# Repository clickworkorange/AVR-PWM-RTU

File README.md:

- <a href="#description">Description</a>
- <a href="#register-map">Register map</a>
- <a href="#avr-pin-map">AVR pin map</a>
- <a href="#defaults">Defaults</a>
- <a href="#crystal-selection">Crystal selection</a>
- <a href="#schematic">Schematic</a>
- <a href="#pcb-layout">PCB layout</a>
- <a href="#the-remote-panels">The remote panels</a>
- <a href="#future">Future</a>
- <a href="#wetware-at-work">Wetware at work</a>

### Description
A Modbus and push-button controlled 4-channel PWM generator based on the Atmel ATMega328. Each channel can be set to one of four pre-defined duty cycles (0-255). In addition to being controllable by Modbus commands, the channel levels (0-3) can also be selected by means of individual push-buttons, wich increment a channel's level, wrapping at 3. The active level for each channel is output as a 2-bit value which is used to drive a set of four LEDs by means of a 74HC238 decoder. The idea is to allow for remote control of the individual channels over a three-wire interface (plus GND and VCC). The Modbus communication layer is provided by the <a href="https://github.com/mbs38/yaMBSiavr">yaMBSiavr</a> library. The code compiles to 9.3kB. 

*N.b. this is still work in progress and some features are yet to be implemented - see <a href="#future">future</a>.*

### Register map
Modbus register values are limited to a maximum value for each register; attempting to write a higher value than what is permitted for a given register will return a 03 ILLEGAL DATA VALUE response from the RTU. The same will happen if you try to write to a read only register. Writing a 1 to the last register (currently 50) will trigger a save to EEPROM of all register values - the RTU will revert to these stored values on reboot. 

#|Function|Value| |#|Function|Value
--|-------------|-----|-|--|-------------|-----
0|Ch0 Level|0-3| |26|Device ID 4-5|2 bytes
1|Ch1 Level|0-3| |27|Device ID 6-7|2 bytes
2|Ch2 Level|0-3| |28|Ch0 ID 0-1|2 bytes
3|Ch3 Level|0-3| |29|Ch0 ID 2-3|2 bytes
4|Ch0 Duty 0|0-255| |30|Ch0 ID 4-5|2 bytes
5|Ch0 Duty 1|0-255| |31|Ch0 ID 6-7|2 bytes
6|Ch0 Duty 2|0-255| |32|Ch1 ID 0-1|2 bytes
7|Ch0 Duty 3|0-255| |33|Ch1 ID 2-3|2 bytes
8|Ch1 Duty 0|0-255| |34|Ch1 ID 4-5|2 bytes
9|Ch1 Duty 1|0-255| |35|Ch1 ID 6-7|2 bytes
10|Ch1 Duty 2|0-255| |36|Ch2 ID 0-1|2 bytes
11|Ch1 Duty 3|0-255| |37|Ch2 ID 2-3|2 bytes
12|Ch2 Duty 0|0-255| |38|Ch2 ID 4-5|2 bytes
13|Ch2 Duty 1|0-255| |39|Ch2 ID 6-7|2 bytes
14|Ch2 Duty 2|0-255| |40|Ch3 ID 0-1|2 bytes
15|Ch2 Duty 3|0-255| |41|Ch3 ID 2-3|2 bytes
16|Ch3 Duty 0|0-255| |42|Ch3 ID 4-5|2 bytes
17|Ch3 Duty 1|0-255| |43|Ch3 ID 6-7|2 bytes
18|Ch3 Duty 2|0-255| |44|Slave Address|0-255
19|Ch3 Duty 3|0-255| |45|Baud Rate|0-7
20|Ch0-1 Invert|0-1| |46|Parity|0-2
21|Ch0-1 Scaler|0-7*| |47|Stop Bits|0-1
22|Ch2-3 Invert|0-1| |48|Firmware Revision|-
23|Ch2-3 Scaler|0-7*| |49|*Reserved*|
24|Device ID 0-1|2 bytes| |50|Save Settings|1/0
25|Device ID 2-3|2 bytes| | | |

\*) See the below table for the meaning of the scaler values:

**Value**|0|1|2|3|4|5|6|7
-----|----|----|----|----|----|----|----|----
**Scaler**|0|1|8|32|64|128|256|1024

Setting either of the scaler registers to zero disables those two channels. See <a href="#crystal-selection">Crystal selection</a> for the PWM frequencies resulting from the different prescalers. Note that at present changes to scalers, inversion and communication parameters requires rebooting the RTU for the changes to take effect. 

### AVR pin map

Pin|Port|Function| |Pin|Port|Function
---|----|-------------|-|---|----|-------------
1|PC6|Reset| |15|PB1|Ch0 PWM
2|PD0|RxD| |16|PB2|Ch1 PWM
3|PD1|TxD| |17|PB3|Ch2 PWM
4|PD2|Data Dir| |18|PB4|Ch3 Lvl LSB
5|PD3|Ch3 PWM| |19|PB5|Ch3 Lvl MSB
6|PD4|Load Defaults| |20|AVCC|+5V
7|Vcc|+5V| |21|AREF|n/c
8|GND|GND| |22|GND|GND
9|PB6|Xtal| |23|PC0|Ch0 Lvl LSB
10|PB7|Xtal| |24|PC1|Ch0 Lvl MSB
11|PD5|Ch2 Btn| |25|PC2|Ch0 Btn
12|PD6|Ch2 Lvl LSB| |26|PC3|Ch1 Lvl LSB
13|PD7|Ch2 Lvl MSB| |27|PC4|Ch1 Lvl MSB
14|PB0|Ch3 Btn| |28|PC5|Ch1 Btn

### Defaults
The default configuration values are: 

- Channel levels all set to 0
- Duty values for levels (all channels)
	- 0: 255
	- 1: 127
	- 2: 63
	- 3: 0
- Both scaler registers set to 4 (490 Hz @ 8 MHz)
- Communication parameters
	- Slave ID: 1
	- Baud: 9600
	- Parity: None
	- Stop bits: 1
 - Identification strings
 	- Device ID: "PWM-1"
  	- Channel IDs: "Ch0", "Ch1", "Ch2", "Ch3"

The RTU can be reset to these values at any time by holding PD4 low on power on / reset. 

### Crystal selection
It's important to pick a system clock frequency that results in the desired PWM frequency for your particular application. If you are controlling fans or other motor driven devices you'll probably want this to be outside human hearing range, if it's lights you'll want it to be high enough for persistence of vision to hide the flicker. Another consideration is the Baud-rate error that will result from choosing a system clock that is not evenly divisible by the desired communication speed. The table below shows the available PWM frequencies for a given clock and prescaler, with Baud-rate compatible clock speeds highlighted in bold: 

Xtal|1|8|32*|64|128*|256|1024
-----------|--------|--------|--------|--------|--------|--------|--------|
2.0000 MHz|7.8 kHz|980 Hz|245 Hz|123 Hz|61 Hz|31 Hz|8 Hz
**3.6864 MHz**|14.5 kHz|1.8 kHz|452 Hz|226 Hz|113 Hz|56 Hz|14 Hz
4.0000 MHz|15.7 kHz|2.0 kHz|490 Hz|245 Hz|123 Hz|61 Hz|15 Hz
**7.3728 MHz**|28.9 kHz|3.6 kHz|904 Hz|452 Hz|226 Hz|113 Hz|28 Hz
8.0000 MHz|31.4 kHz|3.9 kHz|980 Hz|490 Hz|245 Hz|123 Hz|31 Hz
16.0000 MHz|62.7 kHz|7.8 kHz|2.0 kHz|980 Hz|490 Hz|245 Hz|61 Hz
**18.4320 MHz**|72.3 kHz|9.0 kHz|2.3 kHz|1.1 kHz|565 Hz|282 Hz|71 Hz
20.0000 MHz|78.4 kHz|9.8 kHz|2.5 kHz|1.2 kHz|613 Hz|306 Hz|77 Hz

\*) Prescalers 32 & 128 are not available on Timer1, instead we get these by changing the TOP length to 10-bits / scaler 8 and 9-bits / scaler 64 respectively, and <a href="https://github.com/clickworkorange/AVR-PWM-RTU/blob/cd5e14912393d223fffba5abe3af9f1dc7a8ffb7/AVR/avr_pwm_rtu.c#L113-L127">scaling the 0-255 duty value</a> accordingly. 

### Schematic
The schematic has been updated to revision 0.2 and is now presentable - you can find it in [the /KiCAD folder](https://github.com/clickworkorange/AVR-PWM-RTU/tree/main/KiCAD). There will be more changes, not least on the input side, but this should work: 

See <a href="#the-remote-panels">below</a> for the remote panel schematic & PCB layout. 

### PCB layout
The project includes a PCB layout which is sized to fit in a 3U DIN-rail enclosure: 

I have yet to find a good source for multi-level screw terminals with a 3.5mm pitch, but I know they're out there somewhere! You can find the PCB layout together with the schematic in [the /KiCAD folder](https://github.com/clickworkorange/AVR-PWM-RTU/tree/main/KiCAD). 

### The remote panels
The remote panels consist of push-button and four LEDs indicating the channel's level. The LEDs light up incrementally, with one LED lit for level 0 and all four lit at level 3: 

There is also a tiny PCB for it, just 5x3 cm, which should make it easy to fit wherever you want: 

### Future
#### Must:
* Make comms parameters settable through Modbus registers.
#### Should:
* Make a version for the ATMega328PU.
#### Could:
* Apply PWM frequency scalers without reboot.
* Smooth level transitions. 
* Add additional functions for long-press and double-clicks.
* Use the four additional I/Os on the ATMega328PU for feedback.
* Make an MCU based remote with additional features. 
#### Won't:
* Make PWM frequency continuously variable.
* Replace Modbus with a different protocol. 

### Wetware at work
Resistance may indeed be futile, and I for one welcome our new data-based overlords - who I'm sure are paying close attention. But this software was written by a *human*, and only humans can enjoy writing code. Perhaps that joy by itself will one day be seen as an act of <a href="https://en.wikipedia.org/wiki/Joy_as_an_Act_of_Resistance">resistance</a>?

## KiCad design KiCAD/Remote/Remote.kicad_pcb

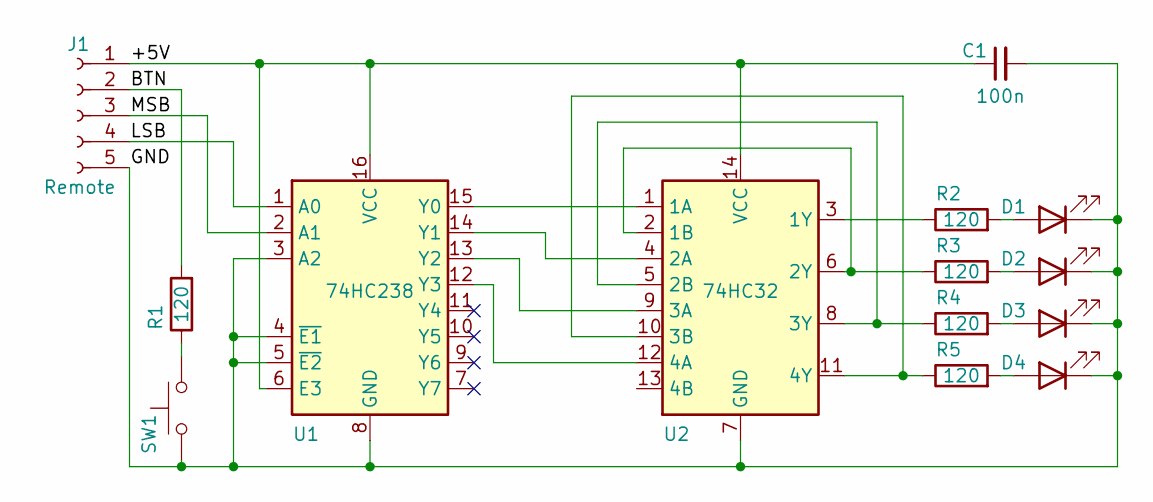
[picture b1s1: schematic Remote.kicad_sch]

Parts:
C1: 100n; C_0805_2012Metric
D1, D2, D3, D4: LED; LED_D3.0mm
J1: Remote; TerminalBlock_Phoenix_PT-1,5-5-3.5-H_1x05_P3.50mm_Horizontal
R1, R2, R3, R4, R5: 120; R_0805_2012Metric
SW1: E-Switch PB300
U1: 74HC238; SOIC-16_3.9x9.9mm_P1.27mm
U2: 74HC32; SOIC-14_3.9x8.7mm_P1.27mm

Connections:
/+5V: C1.1, J1.1, U1.6 (E3), U1.16 (VCC), U2.14 (VCC)
/BTN: J1.2, R1.2
/GND: C1.2, D1.1 (K), D2.1 (K), D3.1 (K), D4.1 (K), J1.5, SW1.1, U1.3 (A2), U1.4 (~E1), U1.5 (~E2), U1.8 (GND), U2.7 (GND)
/LSB: J1.4, U1.1 (A0)
/MSB: J1.3, U1.2 (A1)
unnamed: D1.2 (A), R2.2
unnamed: D2.2 (A), R3.2
unnamed: D3.2 (A), R4.2
unnamed: D4.2 (A), R5.2
unnamed: R1.1, SW1.2
unnamed: R2.1, U2.3 (1Y)
unnamed: R3.1, U2.2 (1B), U2.6 (2Y)
unnamed: R4.1, U2.5 (2B), U2.8 (3Y)
unnamed: U1.12 (Y3), U2.12 (4A)
unnamed: U1.13 (Y2), U2.9 (3A)
unnamed: U1.14 (Y1), U2.4 (2A)
unnamed: U1.15 (Y0), U2.1 (1A)
unnamed: R5.1, U2.10 (3B), U2.11 (4Y)

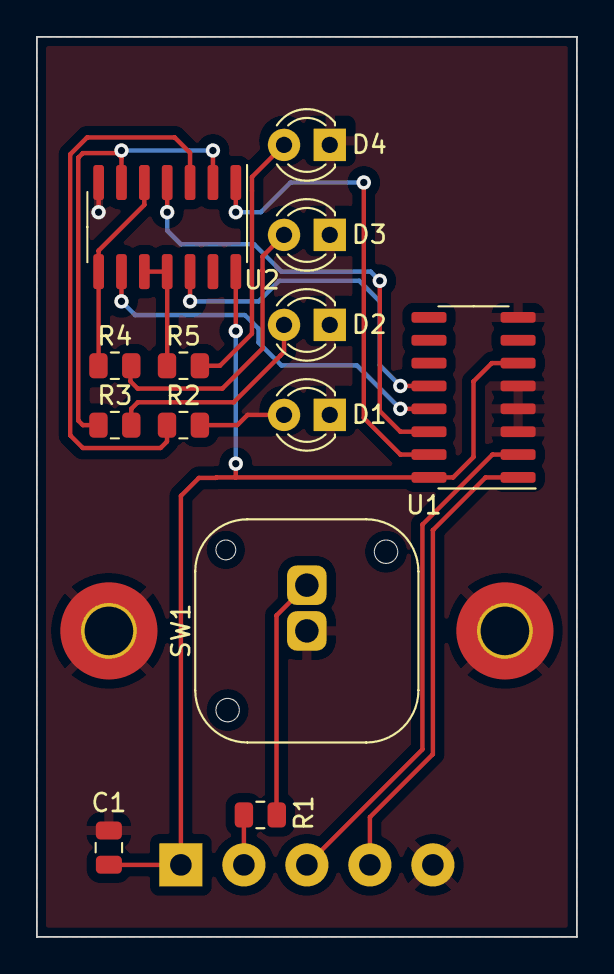
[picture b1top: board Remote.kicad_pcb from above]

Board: 2 copper layers, 30.0 x 50.0 mm, 14 parts (1 on the bottom side), 18 nets.

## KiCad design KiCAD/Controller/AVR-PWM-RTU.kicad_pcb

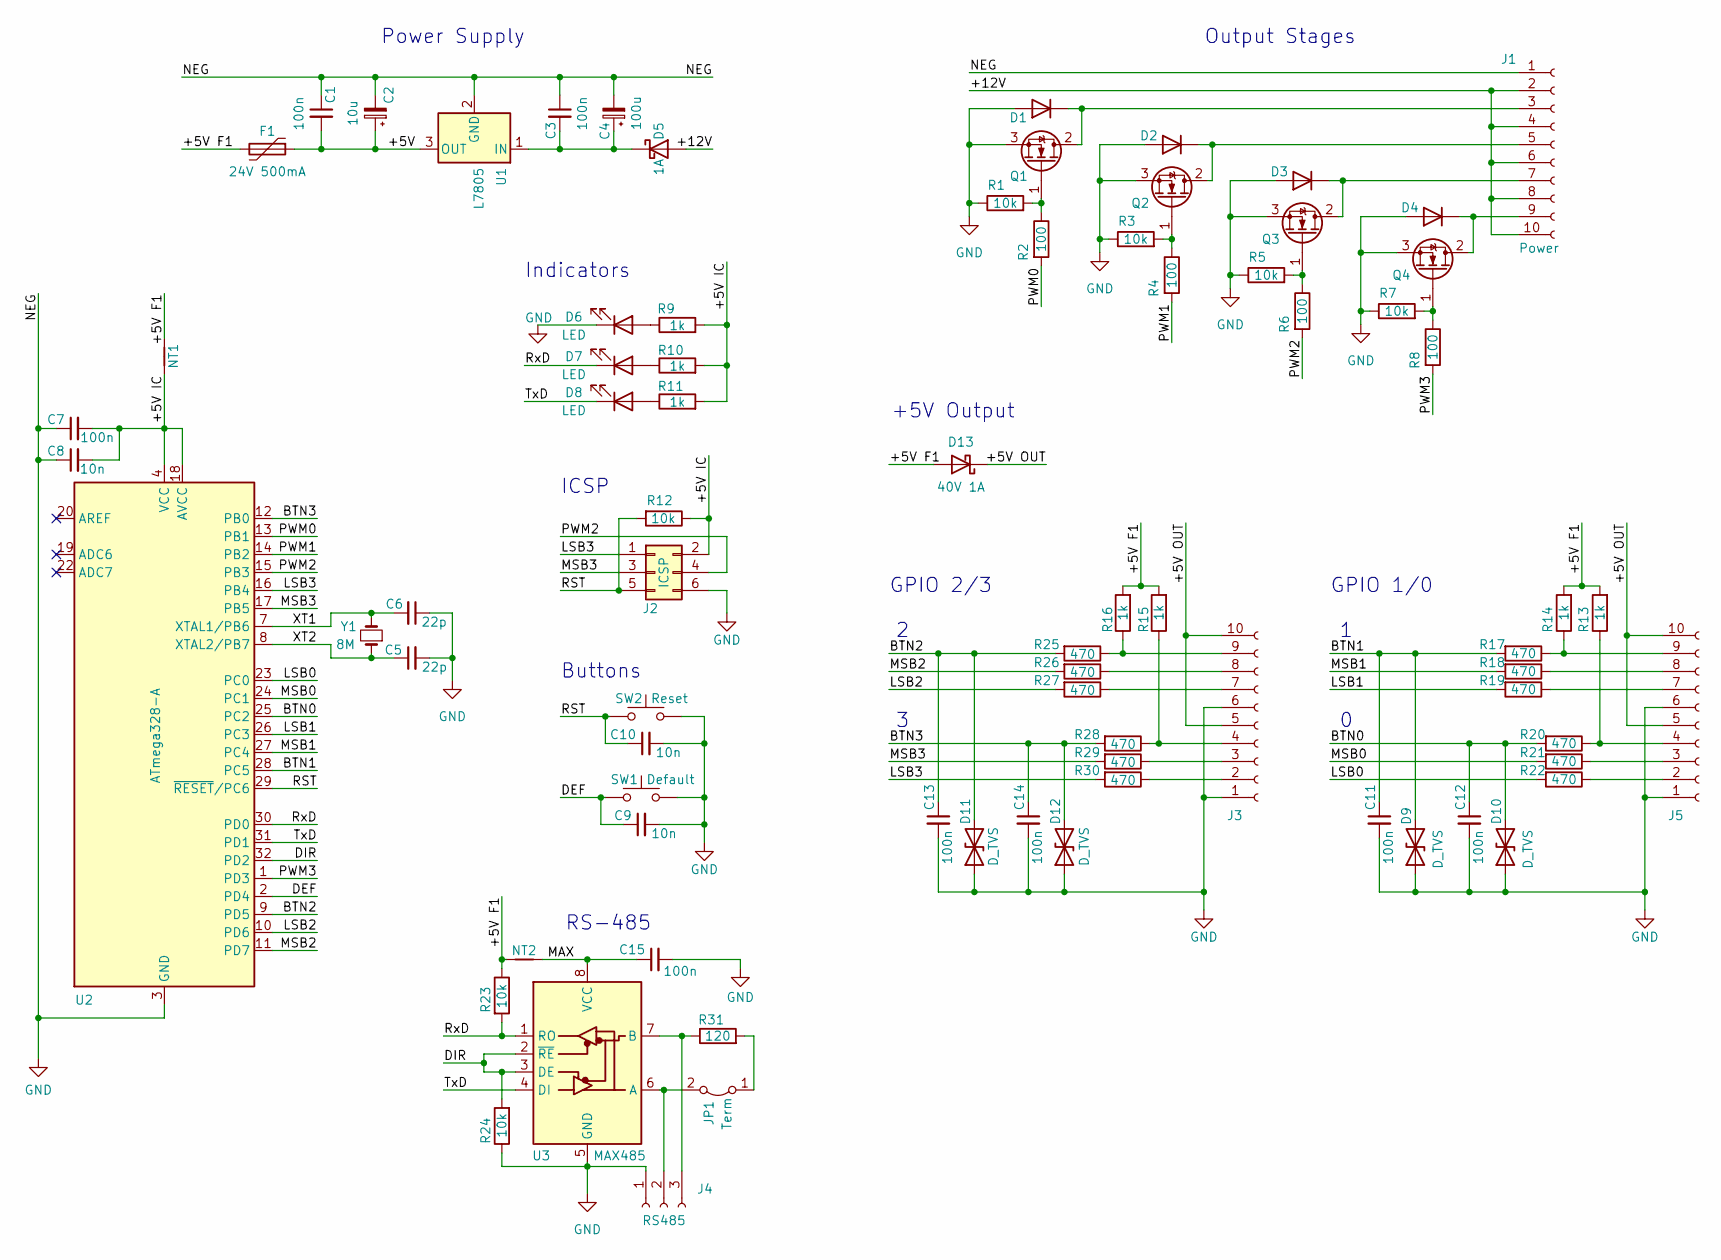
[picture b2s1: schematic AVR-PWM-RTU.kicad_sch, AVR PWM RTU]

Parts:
C1, C3, C7, C11, C12, C13, C14, C15: 100n; C_0805_2012Metric
C2: 10u; C_0805_2012Metric
C4: 100u; CP_Elec_6.3x5.4
C5, C6: 22p; C_0805_2012Metric
C8, C9, C10: 10n; C_0805_2012Metric
D1, D2, D3, D4: D; D_SOD-123
D5: 1A; D_SOD-123
D6, D7, D8: LED; LED_1206_3216Metric
D9, D10, D11, D12: D_TVS; D_0805_2012Metric
D13: 40V 1A; D_SMA
F1: 24V 500mA; R_1206_3216Metric
J1: Power; TerminalBlock_Phoenix_PT-1,5-10-3.5-H_1x10_P3.50mm_Horizont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
J2: ICSP; PinHeader_2x03_P2.54mm_Vertical
J3: TerminalBlock_Phoenix_PT-1,5-10-3.5-H_1x10_P3.50mm_Tall
J4: RS485; TerminalBlock_Phoenix_PT-1,5-3-3.5-H_1x03_P3.50mm_Horizontal
J5: TerminalBlock_Phoenix_PT-1,5-10-3.5-H_1x10_P3.50mm_Horizont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
JP1: Term; PinHeader_1x02_P2.54mm_Vertical
NT1, NT2: NetTie_2; NetTie-2_SMD_Pad0.5mm
Q1, Q2, Q3, Q4: SOT-223-3_TabPin2
R1, R3, R5, R7, R12, R23, R24: 10k; R_0805_2012Metric
R2, R4, R6, R8: 100; R_0805_2012Metric
R9, R10, R11: 1k; R_0805_2012Metric
R13, R14, R15, R16: 1k; R_1206_3216Metric
R17, R18, R19, R20, R21, R22, R25, R26, R27, R28, R29, R30: 470; R_0805_2012Metric
R31: 120; R_0805_2012Metric
SW1: Default; SW_SPST_CK_RS282G05A3
SW2: Reset; SW_SPST_CK_RS282G05A3
U1: L7805; TO-252-2
U2: ATmega328-A; TQFP-32_7x7mm_P0.8mm
U3: MAX485; SOIC-8_3.9x4.9mm_P1.27mm
Y1: 8M; Crystal_SMD_7050-2Pin_7.0x5.0mm

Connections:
/+5V: C1.2, C2.1, F1.1, U1.3 (OUT)
/+5V F1: D13.2 (A), F1.2, NT1.2, NT2.2, R13.2, R14.2, R15.2, R16.2, R23.1
/+5V IC: C7.2, C8.2, J2.2, NT1.1, R9.2, R10.2, R11.2, R12.1, U2.4 (VCC), U2.6 (VCC), U2.18 (AVCC)
/+5V OUT: D13.1 (K), J3.5, J3.10, J5.5, J5.10
/+12V: D5.2 (A), J1.2, J1.4, J1.6, J1.8, J1.10
/BTN0: C12.1, D10.2 (A2), R20.2, U2.25 (PC2)
/BTN1: C11.1, D9.2 (A2), R17.2, U2.28 (PC5)
/BTN2: C13.1, D11.2 (A2), R25.2, U2.9 (PD5)
/BTN3: C14.1, D12.2 (A2), R28.2, U2.12 (PB0)
/DEF: C9.1, SW1.1, U2.2 (PD4)
/DIR: R24.2, U2.32 (PD2), U3.2 (~RE), U3.3 (DE)
/LSB0: R22.2, U2.23 (PC0)
/LSB1: R19.2, U2.26 (PC3)
/LSB2: R27.2, U2.10 (PD6)
/LSB3: J2.1, R30.2, U2.16 (PB4)
/MAX: C15.1, NT2.1, U3.8 (VCC)
/MSB0: R21.2, U2.24 (PC1)
/MSB1: R18.2, U2.27 (PC4)
/MSB2: R26.2, U2.11 (PD7)
/MSB3: J2.3, R29.2, U2.17 (PB5)
/PWM0: R2.2, U2.13 (PB1)
/PWM1: R4.2, U2.14 (PB2)
/PWM2: J2.4, R6.2, U2.15 (PB3)
/PWM3: R8.2, U2.1 (PD3)
/RST: C10.1, J2.5, R12.2, SW2.1, U2.29 (~RESET/PC6)
/RxD: D7.1 (K), R23.2, U2.30 (PD0), U3.1 (RO)
/TxD: D8.1 (K), U2.31 (PD1), U3.4 (DI)
/XT1: C6.2, U2.7 (XTAL1/PB6), Y1.2
/XT2: C5.1, U2.8 (XTAL2/PB7), Y1.1
GND: C1.1, C2.2, C3.1, C4.2, C5.2, C6.1, C7.1, C8.1, C9.2, C10.2, C11.2, C12.2, C13.2, C14.2, C15.2, D1.2 (A), D2.2 (A), D3.2 (A), D4.2 (A), D6.1 (K), D9.1 (A1), D10.1 (A1), D11.1 (A1), D12.1 (A1), J1.1, J2.6, J3.1, J3.6, J4.1, J5.1, J5.6, Q1.3 (S), Q2.3 (S), Q3.3 (S), Q4.3 (S), R1.1, R3.1, R5.1, R7.1, R24.1, SW1.2, SW2.2, U1.2 (GND), U2.3 (GND), U2.5 (GND), U2.21 (GND), U3.5 (GND)
unnamed: C3.2, C4.1, D5.1 (K), U1.1 (IN)
unnamed: D1.1 (K), J1.3, Q1.2 (D)
unnamed: D2.1 (K), J1.5, Q2.2 (D)
unnamed: D3.1 (K), J1.7, Q3.2 (D)
unnamed: D4.1 (K), J1.9, Q4.2 (D)
unnamed: D6.2 (A), R9.1
unnamed: D7.2 (A), R10.1
unnamed: D8.2 (A), R11.1
unnamed: J3.2, R30.1
unnamed: J3.3, R29.1
unnamed: J3.4, R15.1, R28.1
unnamed: J3.7, R27.1
unnamed: J3.8, R26.1
unnamed: J4.2, JP1.2 (B), U3.6 (A)
unnamed: J4.3, R31.1, U3.7 (B)
unnamed: J5.2, R22.1
unnamed: J5.3, R21.1
unnamed: J5.7, R19.1
unnamed: J5.8, R18.1
unnamed: J5.9, R14.1, R17.1
unnamed: JP1.1 (A), R31.2
unnamed: Q1.1 (G), R1.2, R2.1
unnamed: Q2.1 (G), R3.2, R4.1
unnamed: Q3.1 (G), R5.2, R6.1
unnamed: Q4.1 (G), R7.2, R8.1
unnamed: J5.4, R13.1, R20.1
unnamed: J3.9, R16.1, R25.1

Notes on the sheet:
ICSP
RS-485
Output Stages
GPIO 1/0
Buttons
GPIO 2/3
+5V Output
Indicators
Power Supply

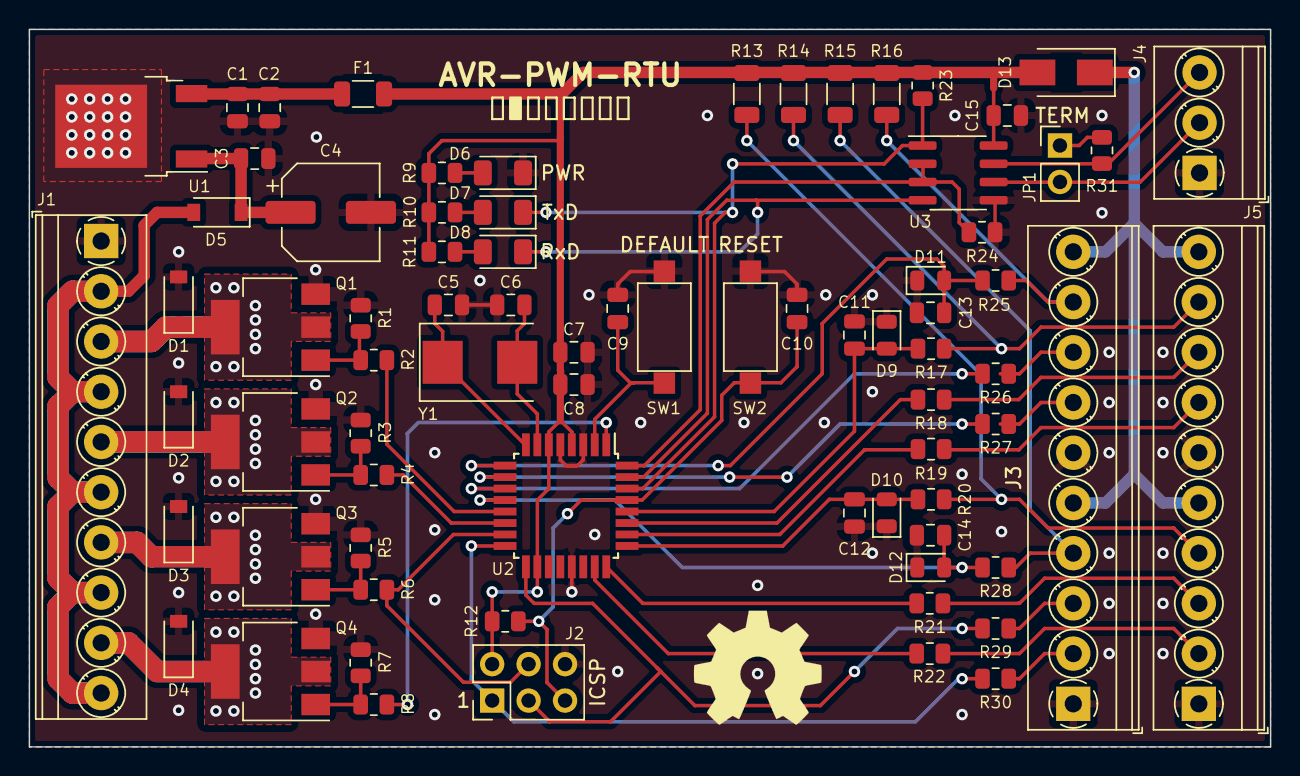
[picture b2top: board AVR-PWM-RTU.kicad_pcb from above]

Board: 2 copper layers, 86.5 x 50.0 mm, 78 parts (0 on the bottom side), 57 nets.

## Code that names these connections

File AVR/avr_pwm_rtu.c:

/*
             |||
            (o o)
 +-------oOO-{_}-OOo--------+
 |                          |
 |   © 2024 Ola Tuvesson    |
 |   clickworkorange Ltd    |
 |                          |
 | info@clickworkorange.com |
 |                          |
 +--------------------------+

*/

#include <string.h>
#include <avr/io.h>
#include <avr/interrupt.h>
#include <avr/wdt.h>
#include <avr/eeprom.h>
#include <util/atomic.h>
#include "avr_pwm_rtu.h"
#include "yaMBSiavr.h"

volatile uint8_t instate = 0;
volatile uint8_t outstate = 0;
volatile uint16_t EEMEM eeprom[REGCOUNT];

static uint16_t registers[REGCOUNT];
static uint16_t rxreg, rxval, rxcnt; 

static uint8_t const BTN0 = 0b00000100; //PORTC
static uint8_t const BTN1 = 0b00100000; //PORTC
static uint8_t const BTN2 = 0b00100000; //PORTD
static uint8_t const BTN3 = 0b00000001; //PORTB
static uint8_t const BTND = 0b00010000; //PORTD

static uint8_t const LED0 = 0b00000011; //PORTC
static uint8_t const LED1 = 0b00011000; //PORTC
static uint8_t const LED2 = 0b11000000; //PORTD
static uint8_t const LED3 = 0b00110000; //PORTB

static uint8_t const PWM0 = 0b00000010; //PORTB
static uint8_t const PWM1 = 0b00000100; //PORTB
static uint8_t const PWM2 = 0b00001000; //PORTB
static uint8_t const PWM3 = 0b00001000; //PORTD

// TODO: this could be more readable... 
static uint8_t const T1WG[] = {0,_BV(WGM10),_BV(WGM10),_BV(WGM10)|_BV(WGM11),_BV(WGM10),_BV(WGM11),_BV(WGM10),_BV(WGM10)};
static uint8_t const T2WG[] = {0,_BV(WGM20)|_BV(WGM21),_BV(WGM20)|_BV(WGM21),_BV(WGM20)|_BV(WGM21),_BV(WGM20)|_BV(WGM21),_BV(WGM20)|_BV(WGM21),_BV(WGM20)|_BV(WGM21),_BV(WGM20)|_BV(WGM21)};
static uint8_t const T1CS[] = {0,_BV(CS10),_BV(CS11),_BV(CS11),_BV(CS10)|_BV(CS11),_BV(CS10)|_BV(CS11),_BV(CS12),_BV(CS10)|_BV(CS12)};
static uint8_t const T2CS[] = {0,_BV(CS20),_BV(CS21),_BV(CS20)|_BV(CS21),_BV(CS22),_BV(CS20)|_BV(CS22),_BV(CS21)|_BV(CS22),_BV(CS20)|_BV(CS21)|_BV(CS22)};

#define OUT(port, led, level) (port ^= (port ^ level) & (led));

void loadRegisters(void) {
	read_register_array(eeprom, registers, REGCOUNT * 2);
}

void saveRegisters(void) {
	if(registers[REGCOUNT-1] == 1) {
		// the last register is the save flag, reset it
		registers[REGCOUNT-1] = 0;
		write_register_array(eeprom, registers, REGCOUNT * 2);
	}
}

void setDefaults(void) {
	if((PIND & BTND) == 0) {
		// if BTND (PD4) is held low, load defaults and save to EEPROM
		memcpy(registers, DEFAULT, REGCOUNT * 2);
		saveRegisters();
	}
}

void pinSetup(void) { 
	// output on B4,B5 (LEDs ch3) & B1,B2,B3 (PWM ch0-2)
	  DDRB = LED3 | PWM0 | PWM1 | PWM2;
	// output on C0,C1 & C3,C4 (LEDs ch0 & 1)
	  DDRC = LED0 | LED1;
	// output on D6,D7 (LEDs ch2) & D3 (PWM ch3)
	  DDRD = LED2 | PWM3;

	// pull-up on B0 (button input ch3)
	 PORTB = BTN3;
	// pull-up on C2,C5 (button inputs ch0 & 1)
	 PORTC = BTN0 | BTN1;
	// pull-up on D5,D4 (button inputs ch2 & defaults)
	 PORTD = BTN2 | BTND;
}

void comSetup(void) {
	modbusSetAddress(registers[44]);
}

void clockSetup(void) {
	// UART clock on Timer0
	TCCR0B = _BV(CS01); // prescaler 8
	TIMSK0 = _BV(TOIE0); // enable overflow interrupt

	// Timer1 (on B1,B2)
	TCCR1A = _BV(COM1A1) | _BV(COM1B1) | registers[20]<<COM1A0 | registers[20]<<COM1B0 | T1WG[registers[21]];
	TCCR1B = _BV(WGM12) | T1CS[registers[21]];

	// Timer2 (on B3,D3)
	TCCR2A = _BV(COM2A1) | _BV(COM2B1) | registers[22]<<COM2A0 | registers[22]<<COM2B0 | T2WG[registers[23]];
	TCCR2B = T2CS[registers[23]];
}

ISR(TIMER0_OVF_vect) { 
	modbusTickTimer();
}

int timerOneLength(int duty) {
	// adjust Timer1 duty for TOP length
	if(TCCR1A & _BV(WGM11)) {
		if(TCCR1A & _BV(WGM10)) {
			// 10-bits (e.g. 127 = 511)
			return duty<<2;
		} else {
			// 9-bits (e.g. 127 = 255)
			return duty<<1;
		}
	} else {
		// 8-bits (no change)
		return duty;
	}
}

void setLevel(uint8_t channel, uint8_t level) {
	registers[channel] = level;
	switch(channel) {
		case 0:
			OCR1A = timerOneLength(registers[4 + level]);
			OUT(PORTC, LED0, registers[0]);
		break;
		case 1:
			OCR1B = timerOneLength(registers[8 + level]);
			OUT(PORTC, LED1, registers[1]<<3);
		break;
		case 2:
			OCR2A = registers[12 + level];
			ATOMIC_BLOCK(ATOMIC_FORCEON) {
				// protect PORTD writes from interrupts
				OUT(PORTD, LED2, registers[2]<<6);
			}
		break;
		case 3:
			OCR2B = registers[16 + level];
			OUT(PORTB, LED3, registers[3]<<4);
		break;
	}
}

void updateLevels(void) {
	for(int i = 0; i < CHANNELS; i++) {
		setLevel(i, registers[i]);
	}
}

void incrChannel(uint8_t channel) {
	setLevel(channel, (registers[channel] + 1) % LEVELS);
}

int validate(uint16_t reg, uint16_t val) {
	if(val < (1<<REGSIZE[reg])) {
		// check if register is read only
		return REGSIZE[reg] != 0; 
	} else {
		return 0;
	}
}

void modbusGet(void) {
	if (modbusGetBusState() & (1<<ReceiveCompleted)) {
		switch(rxbuffer[1]) {
			case fcReadHoldingRegisters: {
				modbusExchangeRegisters(registers,0,REGCOUNT);
				break;
			}
			case fcPresetSingleRegister: {
				rxreg = (rxbuffer[2]<<8) | rxbuffer[3];
				rxval = (rxbuffer[4]<<8) | rxbuffer[5];
				if(validate(rxreg, rxval) == 0) {
					modbusSendException(ecIllegalDataValue);
				}
				modbusExchangeRegisters(registers,0,REGCOUNT);
				updateLevels();
				saveRegisters();
				break;
			}
			case fcPresetMultipleRegisters: {
				rxreg = (rxbuffer[2]<<8) | rxbuffer[3];
				rxcnt = (rxbuffer[4]<<8) | rxbuffer[5];
				for(int i = 0; i < rxcnt; i+=2) {
					rxval = (rxbuffer[7+i]<<8) | rxbuffer[8+i];
					if(validate(rxreg+i, rxval) == 0) {
						modbusSendException(ecIllegalDataValue);
						break;
					} 
				}
				modbusExchangeRegisters(registers,0,REGCOUNT);
				updateLevels();
				saveRegisters();
				break;
			}
			default:
				modbusSendException(ecIllegalFunction);
				break;
		}
	}
}

int main(void) {
	pinSetup();
	setDefaults();
	loadRegisters();
	clockSetup();
	comSetup();
	sei();
	modbusInit();
	wdt_enable(7);
	updateLevels();

	// TODO: make PWM phase configurable
	// TODO: make comm parameters configurable
	while(1) {
		wdt_reset();
		modbusGet();
		if((PINC & BTN0) == 0) {
			incrChannel(0);
			while((PINC & BTN0) == 0); // Wait until the button is released
		}
		if((PINC & BTN1) == 0) {
			incrChannel(1);
			while((PINC & BTN1) == 0);
		}
		if((PIND & BTN2) == 0) {
			incrChannel(2);
			while((PIND & BTN2) == 0);
		}
		if((PINB & BTN3) == 0) {
			incrChannel(3);
			while((PINB & BTN3) == 0);
		}
	}
}

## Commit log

2023-07-26 Tweaked simulation layout Added Simulide screengrab
2023-07-27 Added header file Renamed C files
2023-07-29 Writing a 1 to the last register now triggers save
2024-01-01 Use XOR macro to set level outputs. Protect PORTD writes from interrupts. Use 8MHz clock. Add ATMega328 to yaMBSiavr.h definitions.
2024-01-01 Initial commit of schematic.
2024-01-01 Added schematic preview.
2024-01-05 Added debug target to Makefile.
2024-01-05 Added register value validation.
2024-01-05 Butterfingers.
2024-01-05 Renamed schematic folder to KiCAD.
2024-01-07 Default register values can now be loaded on reset.
2024-01-07 Set PWM frequency scalers from registers.
2024-01-07 Added default identifier strings.
2024-01-07 PWM waveforms can now be inverted.
2024-01-07 Updated schematic.
2024-01-07 Cleaning up.
2024-01-07 Updated compiled files.
2024-02-01 Updated readme.
2024-02-01 Initial commit of PCB layout. Schematic rev.0.2
2024-02-01 Some sexy pictures.
2024-02-04 Added FreeCAD remote panel design.
2024-02-05 Added schematic & PCB for remote. Restructured KiCAD directory.
2024-02-05 Updated README image paths.
2024-02-05 Added information about the remote panels.
2024-02-05 Added 3D view of remote PCB.
2024-02-05 Updated remote schematic.
2024-02-05 Updated remote PCB 3D preview.
